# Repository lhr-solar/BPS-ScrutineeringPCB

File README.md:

# BPS Scrutineering PCB

## Purpose
This board is placed in between the batteries and the [Minion Boards](https://github.com/lhr-solar/BPS-MinionPCB) to allow for scrutineering. In order to use this board properly, you must turn off one switch on the board, apply a voltage between the testpoint for that connection and the one above or below it, and see if the BPS trips. PTC fuses are added to ensure that the Minions Boards are not damaged in case the user does not properly turn off the switch or mishandles the board.

## Connectors
* Four 7 Pin Connectors for feeding voltage measurements

## BOM
https://www.mouser.com/ProjectManager/ProjectDetail.aspx?AccessID=fcc6c80312

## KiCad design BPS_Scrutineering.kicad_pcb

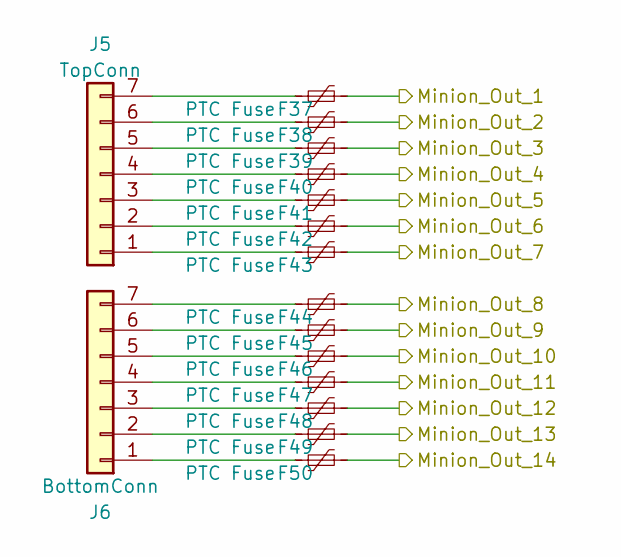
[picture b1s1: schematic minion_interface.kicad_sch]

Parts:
F37, F38, F39, F40, F41, F42, F43, F44, F45, F46, F47, F48, F49, F50: PTC Fuse; FUSC1810X100N
J5: TopConn; Molex_Micro-Fit_3.0_43650-0700_1x07_P3.00mm_Horizontal
J6: BottomConn; Molex_Micro-Fit_3.0_43650-0700_1x07_P3.00mm_Horizontal

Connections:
/BPS_MINION_1/Minion_Out_1: F37.2; also elsewhere on the board
/BPS_MINION_1/Minion_Out_2: F38.2; also elsewhere on the board
/BPS_MINION_1/Minion_Out_3: F39.2; also elsewhere on the board
/BPS_MINION_1/Minion_Out_4: F40.2; also elsewhere on the board
/BPS_MINION_1/Minion_Out_5: F41.2; also elsewhere on the board
/BPS_MINION_1/Minion_Out_6: F42.2; also elsewhere on the board
/BPS_MINION_1/Minion_Out_7: F43.2; also elsewhere on the board
/BPS_MINION_1/Minion_Out_8: F44.2; also elsewhere on the board
/BPS_MINION_1/Minion_Out_9: F45.2; also elsewhere on the board
/BPS_MINION_1/Minion_Out_10: F46.2; also elsewhere on the board
/BPS_MINION_1/Minion_Out_11: F47.2; also elsewhere on the board
/BPS_MINION_1/Minion_Out_12: F48.2; also elsewhere on the board
unnamed: F43.1, J5.1
unnamed: F42.1, J5.2
unnamed: F41.1, J5.3
unnamed: F40.1, J5.4
unnamed: F39.1, J5.5
unnamed: F38.1, J5.6
unnamed: F37.1, J5.7
unnamed: F48.1, J6.3
unnamed: F47.1, J6.4
unnamed: F46.1, J6.5
unnamed: F45.1, J6.6
unnamed: F44.1, J6.7

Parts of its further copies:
F51, F52, F53, F54, F55, F56, F57, F58, F59, F60, F61, F65, F66, F67, F68, F69, F70, F71, F72, F73, F74, F75, F76: PTC Fuse; FUSC1810X100N
J7, J9: TopConn; Molex_Micro-Fit_3.0_43650-0700_1x07_P3.00mm_Horizontal
J8, J10: BottomConn; Molex_Micro-Fit_3.0_43650-0700_1x07_P3.00mm_Horizontal

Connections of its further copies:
/BPS_MINION_2/Minion_Out_1: F51.2; also elsewhere on the board
/BPS_MINION_2/Minion_Out_2: F52.2; also elsewhere on the board
/BPS_MINION_2/Minion_Out_3: F53.2; also elsewhere on the board
/BPS_MINION_2/Minion_Out_4: F54.2; also elsewhere on the board
/BPS_MINION_2/Minion_Out_5: F55.2; also elsewhere on the board
/BPS_MINION_2/Minion_Out_6: F56.2; also elsewhere on the board
/BPS_MINION_2/Minion_Out_7: F57.2; also elsewhere on the board
/BPS_MINION_2/Minion_Out_8: F58.2; also elsewhere on the board
/BPS_MINION_2/Minion_Out_9: F59.2; also elsewhere on the board
/BPS_MINION_2/Minion_Out_10: F60.2; also elsewhere on the board
/BPS_MINION_2/Minion_Out_11: F61.2; also elsewhere on the board
/BPS_MINION_3/Minion_Out_1: F65.2; also elsewhere on the board
/BPS_MINION_3/Minion_Out_2: F66.2; also elsewhere on the board
/BPS_MINION_3/Minion_Out_3: F67.2; also elsewhere on the board
/BPS_MINION_3/Minion_Out_4: F68.2; also elsewhere on the board
/BPS_MINION_3/Minion_Out_5: F69.2; also elsewhere on the board
/BPS_MINION_3/Minion_Out_6: F70.2; also elsewhere on the board
/BPS_MINION_3/Minion_Out_7: F71.2; also elsewhere on the board
/BPS_MINION_3/Minion_Out_8: F72.2; also elsewhere on the board
/BPS_MINION_3/Minion_Out_9: F73.2; also elsewhere on the board
/BPS_MINION_3/Minion_Out_10: F74.2; also elsewhere on the board
/BPS_MINION_3/Minion_Out_11: F75.2; also elsewhere on the board
/BPS_MINION_3/Minion_Out_12: F76.2; also elsewhere on the board
unnamed: F57.1, J7.1
unnamed: F56.1, J7.2
unnamed: F55.1, J7.3
unnamed: F54.1, J7.4
unnamed: F53.1, J7.5
unnamed: F52.1, J7.6
unnamed: F51.1, J7.7
unnamed: F61.1, J8.4
unnamed: F60.1, J8.5
unnamed: F59.1, J8.6
unnamed: F58.1, J8.7
unnamed: F71.1, J9.1
unnamed: F70.1, J9.2
unnamed: F69.1, J9.3
unnamed: F68.1, J9.4
unnamed: F67.1, J9.5
unnamed: F66.1, J9.6
unnamed: F65.1, J9.7
unnamed: F76.1, J10.3
unnamed: F75.1, J10.4
unnamed: F74.1, J10.5
unnamed: F73.1, J10.6
unnamed: F72.1, J10.7

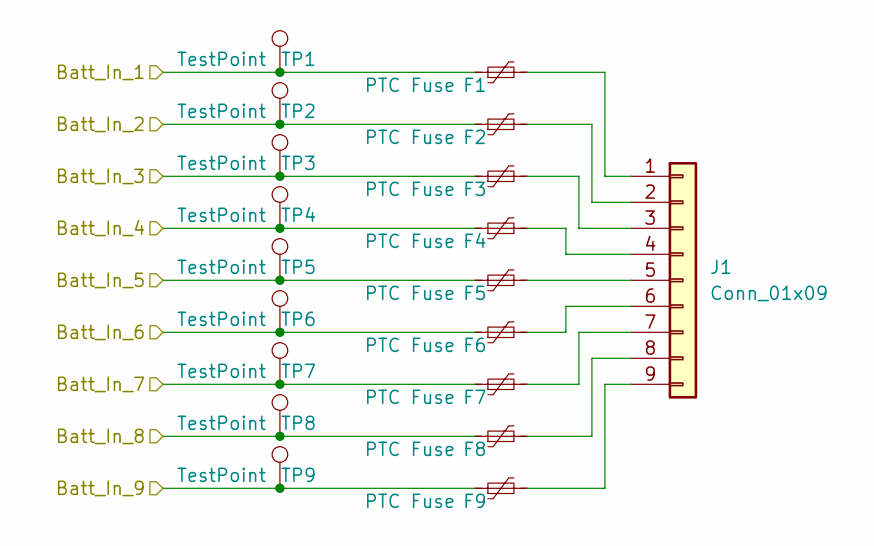
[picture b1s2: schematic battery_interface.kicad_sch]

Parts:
F1, F2, F3, F4, F5, F6, F7, F8, F9: PTC Fuse; FUSC1810X100N
J1: Conn_01x09; Molex_Micro-Fit_3.0_43650-0915_1x09_P3.00mm_Vertical
TP1, TP2, TP3, TP4, TP5, TP6, TP7, TP8, TP9: TestPoint; TestPoint_Keystone_5005-5009_Compact

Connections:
/1+_BATT: F2.1, TP2.1; also elsewhere on the board
/1-_BATT: F1.1, TP1.1; also elsewhere on the board
/2+_BATT: F3.1, TP3.1; also elsewhere on the board
/3+_BATT: F4.1, TP4.1; also elsewhere on the board
/4+_BATT: F5.1, TP5.1; also elsewhere on the board
/5+_BATT: F6.1, TP6.1; also elsewhere on the board
/6+_BATT: F7.1, TP7.1; also elsewhere on the board
/7+_BATT: F8.1, TP8.1; also elsewhere on the board
/8+_BATT: F9.1, TP9.1; also elsewhere on the board
unnamed: F1.2, J1.1
unnamed: F2.2, J1.2
unnamed: F3.2, J1.3
unnamed: F4.2, J1.4
unnamed: F5.2, J1.5
unnamed: F6.2, J1.6
unnamed: F7.2, J1.7
unnamed: F8.2, J1.8
unnamed: F9.2, J1.9

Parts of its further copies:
F10, F11, F12, F13, F14, F15, F16, F17, F18, F19, F20, F21, F22, F23, F24, F25, F26, F27, F28, F29, F30, F31, F32, F33, F34, F35, F36: PTC Fuse; FUSC1810X100N
J2, J3, J4: Conn_01x09; Molex_Micro-Fit_3.0_43650-0915_1x09_P3.00mm_Vertical
TP10, TP11, TP12, TP13, TP14, TP15, TP16, TP17, TP18, TP19, TP20, TP21, TP22, TP23, TP24, TP25, TP26, TP27, TP28, TP29, TP30, TP31, TP32, TP33, TP34, TP35, TP36: TestPoint; TestPoint_Keystone_5005-5009_Compact

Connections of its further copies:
/9+_BATT: F11.1, TP11.1; also elsewhere on the board
/9-_BATT: F10.1, TP10.1
/10+_BATT: F12.1, TP12.1; also elsewhere on the board
/11+_BATT: F13.1, TP13.1; also elsewhere on the board
/12+_BATT: F14.1, TP14.1; also elsewhere on the board
/13+_BATT: F15.1, TP15.1; also elsewhere on the board
/14+_BATT: F16.1, TP16.1; also elsewhere on the board
/15+_BATT: F17.1, TP17.1; also elsewhere on the board
/16+_BATT: F18.1, TP18.1; also elsewhere on the board
/17+_BATT: F20.1, TP20.1; also elsewhere on the board
/17-_BATT: F19.1, TP19.1
/18+_BATT: F21.1, TP21.1; also elsewhere on the board
/19+_BATT: F22.1, TP22.1; also elsewhere on the board
/20+_BATT: F23.1, TP23.1; also elsewhere on the board
/21+_BATT: F24.1, TP24.1; also elsewhere on the board
/22+_BATT: F25.1, TP25.1; also elsewhere on the board
/23+_BATT: F26.1, TP26.1; also elsewhere on the board
/24+_BATT: F27.1, TP27.1; also elsewhere on the board
/25+_BATT: F29.1, TP29.1; also elsewhere on the board
/25-_BATT: F28.1, TP28.1
/26+_BATT: F30.1, TP30.1; also elsewhere on the board
/27+_BATT: F31.1, TP31.1; also elsewhere on the board
/28+_BATT: F32.1, TP32.1; also elsewhere on the board
/29+_BATT: F33.1, TP33.1; also elsewhere on the board
/30+_BATT: F34.1, TP34.1; also elsewhere on the board
/31+_BATT: F35.1, TP35.1; also elsewhere on the board
/32+_BATT: F36.1, TP36.1; also elsewhere on the board
unnamed: F10.2, J2.1
unnamed: F11.2, J2.2
unnamed: F12.2, J2.3
unnamed: F13.2, J2.4
unnamed: F14.2, J2.5
unnamed: F15.2, J2.6
unnamed: F16.2, J2.7
unnamed: F17.2, J2.8
unnamed: F18.2, J2.9
unnamed: F19.2, J3.1
unnamed: F20.2, J3.2
unnamed: F21.2, J3.3
unnamed: F22.2, J3.4
unnamed: F23.2, J3.5
unnamed: F24.2, J3.6
unnamed: F25.2, J3.7
unnamed: F26.2, J3.8
unnamed: F27.2, J3.9
unnamed: F28.2, J4.1
unnamed: F29.2, J4.2
unnamed: F30.2, J4.3
unnamed: F31.2, J4.4
unnamed: F32.2, J4.5
unnamed: F33.2, J4.6
unnamed: F34.2, J4.7
unnamed: F35.2, J4.8
unnamed: F36.2, J4.9

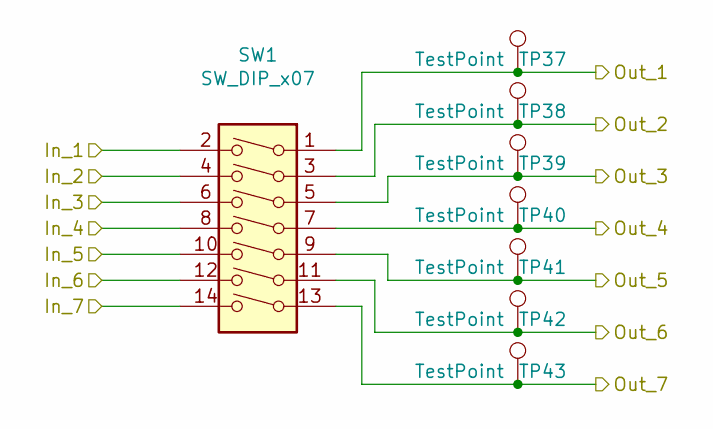
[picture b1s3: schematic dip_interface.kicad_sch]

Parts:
SW1: SW_DIP_x07; 7switch_module_DS04254207BKSMT
TP37, TP38, TP39, TP40, TP41, TP42, TP43: TestPoint; TestPoint_Keystone_5005-5009_Compact

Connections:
/1+_BATT: SW1.4; also elsewhere on the board
/1-_BATT: SW1.2; also elsewhere on the board
/2+_BATT: SW1.6; also elsewhere on the board
/3+_BATT: SW1.8; also elsewhere on the board
/4+_BATT: SW1.10; also elsewhere on the board
/5+_BATT: SW1.12; also elsewhere on the board
/6+_BATT: SW1.14; also elsewhere on the board
/BPS_MINION_1/Minion_Out_1: SW1.1, TP37.1; also elsewhere on the board
/BPS_MINION_1/Minion_Out_2: SW1.3, TP38.1; also elsewhere on the board
/BPS_MINION_1/Minion_Out_3: SW1.5, TP39.1; also elsewhere on the board
/BPS_MINION_1/Minion_Out_4: SW1.7, TP40.1; also elsewhere on the board
/BPS_MINION_1/Minion_Out_5: SW1.9, TP41.1; also elsewhere on the board
/BPS_MINION_1/Minion_Out_6: SW1.11, TP42.1; also elsewhere on the board
/BPS_MINION_1/Minion_Out_7: SW1.13, TP43.1; also elsewhere on the board

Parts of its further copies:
SW2, SW3, SW4, SW5, SW6: SW_DIP_x07; 7switch_module_DS04254207BKSMT
TP44, TP45, TP46, TP47, TP48, TP51, TP52, TP53, TP54, TP55, TP56, TP57, TP58, TP59, TP60, TP61, TP65, TP66, TP67, TP68, TP69, TP70, TP71, TP72, TP73, TP74, TP75, TP76: TestPoint; TestPoint_Keystone_5005-5009_Compact

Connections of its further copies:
/7+_BATT: SW2.2; also elsewhere on the board
/8+_BATT: SW2.4; also elsewhere on the board
/9+_BATT: SW2.6; also elsewhere on the board
/10+_BATT: SW2.8; also elsewhere on the board
/11+_BATT: SW2.10, SW3.2; also elsewhere on the board
/12+_BATT: SW3.4; also elsewhere on the board
/13+_BATT: SW3.6; also elsewhere on the board
/14+_BATT: SW3.8; also elsewhere on the board
/15+_BATT: SW3.10; also elsewhere on the board
/16+_BATT: SW3.12; also elsewhere on the board
/17+_BATT: SW3.14; also elsewhere on the board
/18+_BATT: SW4.2; also elsewhere on the board
/19+_BATT: SW4.4; also elsewhere on the board
/20+_BATT: SW4.6; also elsewhere on the board
/21+_BATT: SW4.8, SW5.2; also elsewhere on the board
/22+_BATT: SW5.4; also elsewhere on the board
/23+_BATT: SW5.6; also elsewhere on the board
/24+_BATT: SW5.8; also elsewhere on the board
/25+_BATT: SW5.10; also elsewhere on the board
/26+_BATT: SW5.12; also elsewhere on the board
/27+_BATT: SW5.14; also elsewhere on the board
/28+_BATT: SW6.2; also elsewhere on the board
/29+_BATT: SW6.4; also elsewhere on the board
/30+_BATT: SW6.6; also elsewhere on the board
/31+_BATT: SW6.8; also elsewhere on the board
/32+_BATT: SW6.10; also elsewhere on the board
/BPS_MINION_1/Minion_Out_8: SW2.1, TP44.1; also elsewhere on the board
/BPS_MINION_1/Minion_Out_9: SW2.3, TP45.1; also elsewhere on the board
/BPS_MINION_1/Minion_Out_10: SW2.5, TP46.1; also elsewhere on the board
/BPS_MINION_1/Minion_Out_11: SW2.7, TP47.1; also elsewhere on the board
/BPS_MINION_1/Minion_Out_12: SW2.9, TP48.1; also elsewhere on the board
/BPS_MINION_2/Minion_Out_1: SW3.1, TP51.1; also elsewhere on the board
/BPS_MINION_2/Minion_Out_2: SW3.3, TP52.1; also elsewhere on the board
/BPS_MINION_2/Minion_Out_3: SW3.5, TP53.1; also elsewhere on the board
/BPS_MINION_2/Minion_Out_4: SW3.7, TP54.1; also elsewhere on the board
/BPS_MINION_2/Minion_Out_5: SW3.9, TP55.1; also elsewhere on the board
/BPS_MINION_2/Minion_Out_6: SW3.11, TP56.1; also elsewhere on the board
/BPS_MINION_2/Minion_Out_7: SW3.13, TP57.1; also elsewhere on the board
/BPS_MINION_2/Minion_Out_8: SW4.1, TP58.1; also elsewhere on the board
/BPS_MINION_2/Minion_Out_9: SW4.3, TP59.1; also elsewhere on the board
/BPS_MINION_2/Minion_Out_10: SW4.5, TP60.1; also elsewhere on the board
/BPS_MINION_2/Minion_Out_11: SW4.7, TP61.1; also elsewhere on the board
/BPS_MINION_3/Minion_Out_1: SW5.1, TP65.1; also elsewhere on the board
/BPS_MINION_3/Minion_Out_2: SW5.3, TP66.1; also elsewhere on the board
/BPS_MINION_3/Minion_Out_3: SW5.5, TP67.1; also elsewhere on the board
/BPS_MINION_3/Minion_Out_4: SW5.7, TP68.1; also elsewhere on the board
/BPS_MINION_3/Minion_Out_5: SW5.9, TP69.1; also elsewhere on the board
/BPS_MINION_3/Minion_Out_6: SW5.11, TP70.1; also elsewhere on the board
/BPS_MINION_3/Minion_Out_7: SW5.13, TP71.1; also elsewhere on the board
/BPS_MINION_3/Minion_Out_8: SW6.1, TP72.1; also elsewhere on the board
/BPS_MINION_3/Minion_Out_9: SW6.3, TP73.1; also elsewhere on the board
/BPS_MINION_3/Minion_Out_10: SW6.5, TP74.1; also elsewhere on the board
/BPS_MINION_3/Minion_Out_11: SW6.7, TP75.1; also elsewhere on the board
/BPS_MINION_3/Minion_Out_12: SW6.9, TP76.1; also elsewhere on the board
/DIP_SW_2/In_6: SW2.12
/DIP_SW_2/In_7: SW2.14
/DIP_SW_2/Out_6: SW2.11
/DIP_SW_2/Out_7: SW2.13
/DIP_SW_4/In_5: SW4.10
/DIP_SW_4/In_6: SW4.12
/DIP_SW_4/In_7: SW4.14
/DIP_SW_4/Out_5: SW4.9
/DIP_SW_4/Out_6: SW4.11
/DIP_SW_4/Out_7: SW4.13
/DIP_SW_6/In_6: SW6.12
/DIP_SW_6/In_7: SW6.14
/DIP_SW_6/Out_6: SW6.11
/DIP_SW_6/Out_7: SW6.13

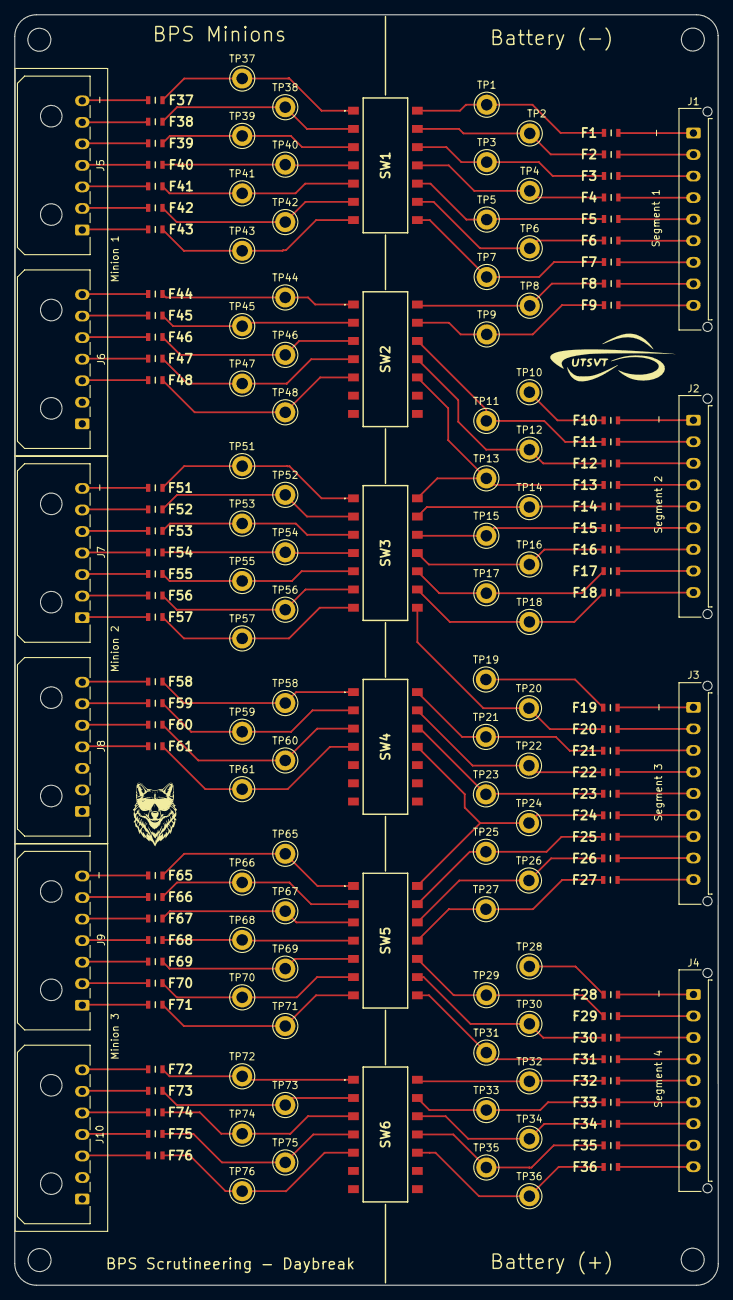
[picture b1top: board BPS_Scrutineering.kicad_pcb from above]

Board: 2 copper layers, 98.0 x 177.0 mm, 158 parts (0 on the bottom side), 142 nets.

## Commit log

2020-08-02 Set up for own repository
2020-08-02 Updates gitignore
2020-10-03 Adds QuAC
2020-10-19 ready for peer review
2020-11-07 schematic done, editing PCB, number of banana jacks?
2020-11-14 finished PCB
2020-11-14 PCB finished
2020-11-14 Flipped Connectors
2020-11-14 Changed footprints
2020-11-21 Cleaned up tracks and got rid of references, waiting for footprint
2020-11-21 new jacks, redid traces, fixed Hannah's comments
2020-12-18 Fix issues with connector sizes and wiring
2020-12-19 Add banana connector key to the board
2020-12-20 Updates common repo
2021-01-06 Adds names and adds labels to logos on schematic
2021-01-06 Organizes gerber files
2021-02-06 Updates common folder
2021-02-06 adds 3d model
2022-09-27 Added PTC fuses and checkpoints in schematic to protect against short circuit btwn power supply and battery module
2022-10-01 Added PTC fuses along all molex connectors, updated datasheet links, and updated component footprints
2022-10-01 Added BOM
2022-11-08 Almost done with laying out the PCB. Replaced the banana connectors with test points
2022-11-08 Complete draft of PCB layout
2022-11-08 Aligned board to grid and added measurements
2022-11-12 Updated BOM with mouser project cart link. Other minor changes to schematic/layout
2022-11-12 Actual commit with the bom and cart lmao
2022-11-12 Added gerber and drill files
2023-02-01 Changed testpoint footprints to match commonly-used testpoints
2023-02-02 Removed old gerber files, added new gerber zip file, updated .gitignore to ignore more backup files and directories
2023-02-04 Generated separate NPTH and PTH drill files; Updated bom
2023-02-20 Updated molex connector part in schematic and bom
2023-05-07 Standardized repository
2023-05-07 Fix merge conflicts
2024-10-09 Finished Schematic
2024-10-09 Updated .gitignore
2024-10-09 Updated no connects
2024-10-09 twoWolves
2024-10-09 fixed spacing and schematic
2024-10-09 Added traces and edge cuts
2024-10-14 gerbers
